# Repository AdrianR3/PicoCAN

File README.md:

# PicoCAN
PicoCAN is a custom devboard based on the RP2040 that features a built-in CAN controller and transceiver (the `MCP25625` to be exact).

## Key Features
- USB-C connection for easy programming
- RP2040 based, with the same size as the Pi Pico
- CAN BUS using MCP25625
  - Built-in 120Ω termination resistor, which can be enabled by bridging the two pins near the `CANL` pin
- Support for powering with 5V through `VSYS` pin
- 28 usable GPIO pins, including 4 ADC pins
- Two on-board LEDs (Green and Red)
  - The red LED also shares pin `24` on the board
  - The green LED is not connected to any of the PicoCAN's pins

## Using the CAN bus

To interface with the CAN bus, you can use any library that supports the MCP25625. There are a few examples that use the [MCP_CAN](https://github.com/coryjfowler/MCP_CAN_lib) library in the `./firmware_examples` folder; they are adapted from https://github.com/coryjfowler/MCP_CAN_lib.

## Building the PicoCAN
The PicoCAN can be ordered from sites like JLCPCB (and optionally assembled too). The KiCAD source files are in `./KiCAD` and the production gerber files are in `./KiCAD/prod` along with the bom.

This is what JLC PCBA gets you! These don't have the headers soldered on yet.

## Images

## Schematic

## BOM

| Name                                                                           | Purpose                                                                  | Quantity | Total Cost (USD) | Link                                                                                                                                                                                                                                                                                                                                                                                                                                                                                                                     | Distributor |
| ------------------------------------------------------------------------------ | ------------------------------------------------------------------------ | -------- | ---------------- | ------------------------------------------------------------------------------------------------------------------------------------------------------------------------------------------------------------------------------------------------------------------------------------------------------------------------------------------------------------------------------------------------------------------------------------------------------------------------------------------------------------------------ | ----------- |
| 10kΩ Resistors                                                                 | JLCPCB idle parts order to avoid ~8000 MOQ                               | 15       | 2.00             | https://jlcpcb.com/partdetail/26487-0402WGF1002TCE/C25744                                                                                                                                                                                                                                                                                                                                                                                                                                                                | JLCPCB      |
| JLCPCB PCB(A)                                                                  | PCBA for the devboard                                                    |          | 74.30            |                                                                                                                                                                                                                                                                                                                                                                                                                                                                                                                          | JLCPCB      |
| Breakaway 2.54mm Headers                                                       | Soldering to PCB for GPIO, Termination Resistor Jumper, SWD + SWCLK pins | 220      | 5.73             | https://www.amazon.com/Jabinco-Breakable-Header-Connector-Arduino/dp/B0817JG3XN/ref=sr_1_3?crid=2WKRDMD09IP3A&dib=eyJ2IjoiMSJ9.czj50ypkQJ1W7noQLo1BweZEBilxaPpO0ntqUIsbMOZ8NaUK7SirIiKj0zqjNVH7wel-Muxf7cilYZ1Gkm4LgajcBaFuuT2h6h5A3zPeYstX5vvQowuI_TuSg0Kxc1e53BEuy5Jd69yTYBwJ_uQCerRUqfk7djKjaq9QYkqNW6D93iLd-X65YBIYgty5NQg0PXmwjQjx0RvcIDNsFUhAgsMDf7z5tFzePYIG2SYMh9Q.pCbw9QGeBexphDohe_PNYFXcjPvPNsFaeCrxSnrcMaw&dib_tag=se&keywords=2.54mm+pin+header&qid=1775094589&sprefix=2.54mm+pin+header%2Caps%2C168&sr=8-3 | Amazon      |
| Socket Shorting Block Jumper Red Closed                                        | Enabling Termination Resistor built into PCB (MOQ 10)                    | 5        | 1.40             | https://www.jameco.com/webapp/wcs/stores/servlet/ProductDisplay?storeId=10001&langId=-1&catalogId=10001&pa=112432&productId=112432                                                                                                                                                                                                                                                                                                                                                                                       | Jameco      |
| Terminal Block Header 3 Position Top Screw 3.5mm Solder Straight Thru-Hole 10A | Connecting to CAN BUS (CANL, CANH, GND)                                  | 5        | 3.95             | https://www.jameco.com/webapp/wcs/stores/servlet/ProductDisplay?storeId=10001&langId=-1&catalogId=10001&pa=2094514&productId=2094514                                                                                                                                                                                                                                                                                                                                                                                     | Jameco      |

Exhaustive PCB component BOM available at `./KiCAD/prod/PicoCAN.csv`.

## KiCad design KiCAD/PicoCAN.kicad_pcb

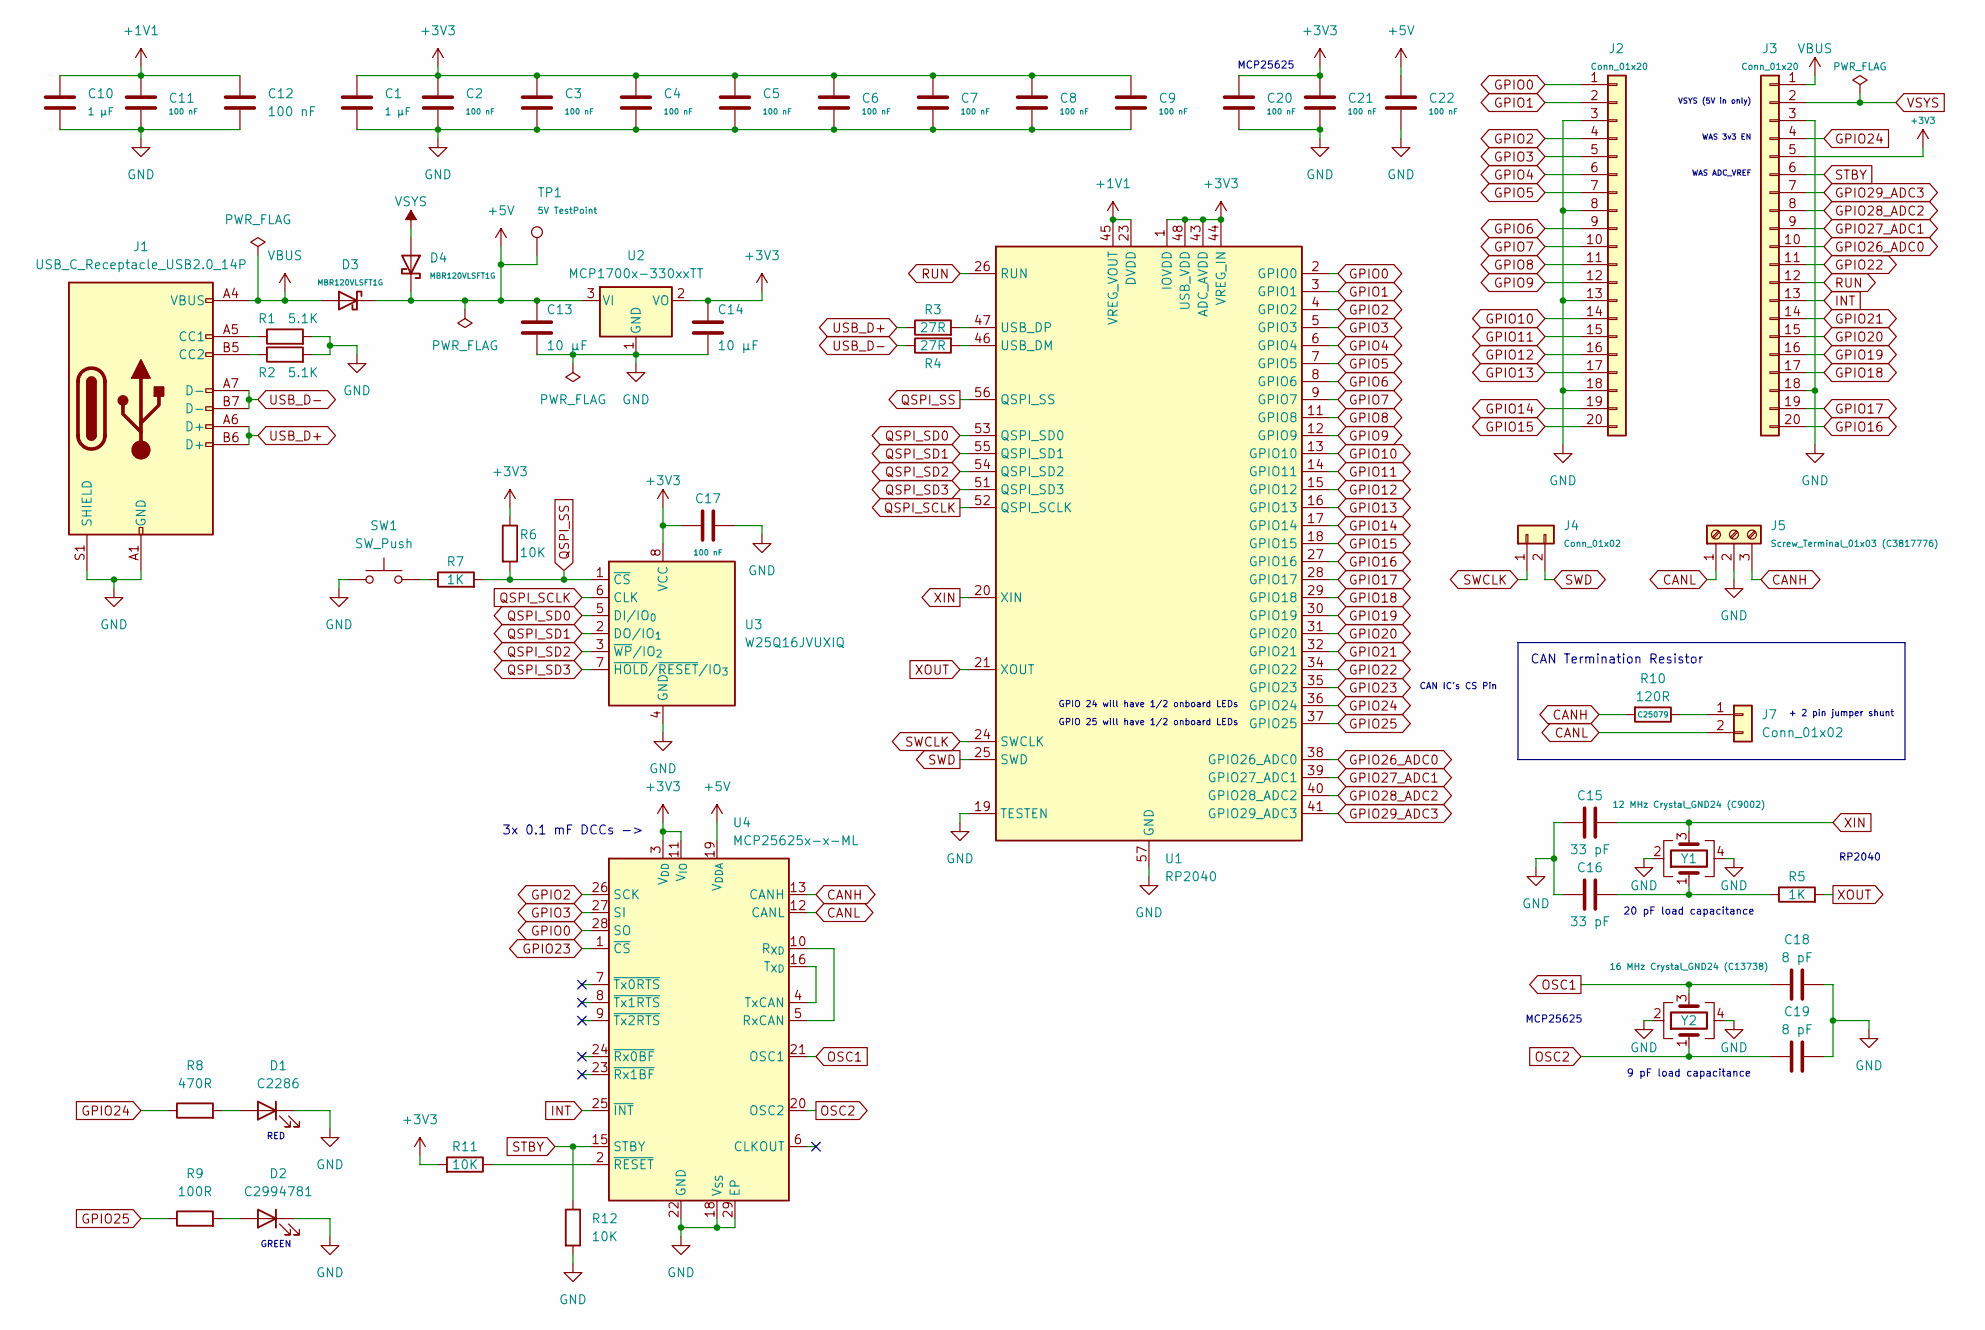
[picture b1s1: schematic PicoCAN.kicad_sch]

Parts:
C1, C10: 1 µF; C_0402_1005Metric; MPN C52923
C2, C3, C4, C5, C6, C7, C8, C9, C11, C12, C17, C20, C21, C22: 100 nF; C_0402_1005Metric; MPN C1525
C13, C14: 10 µF; C_0603_1608Metric; MPN C96446
C15, C16: 33 pF; C_0402_1005Metric; MPN C1562
C18, C19: 8 pF; C_0402_1005Metric; MPN C1578
D1: C2286; LED_0603_1608Metric_Pad1.05x0.95mm_HandSolder; MPN C2286
D2: C2994781; LED_0603_1608Metric_Pad1.05x0.95mm_HandSolder; MPN C2994781
D3, D4: MBR120VLSFT1G; D_SOD-123F; MPN C223608
J1: USB_C_Receptacle_USB2.0_14P; USB_C_Receptacle_HRO_TYPE-C-31-M-12; MPN C165948
J2, J3: Conn_01x20; PinHeader_1x20_P2.54mm_Vertical
J4, J7: Conn_01x02; PinHeader_1x02_P2.54mm_Vertical
J5: Screw_Terminal_01x03 (C3817776); CONN-TH_3P-P3.50_OSTTE030161; MPN C3817776
R1, R2: 5.1K; R_0402_1005Metric; MPN C25905
R3, R4: 27R; R_0402_1005Metric; MPN C25100
R5, R7: 1K; R_0402_1005Metric; MPN C11702
R6, R11, R12: 10K; R_0402_1005Metric; MPN C25744
R8: 470R; R_0402_1005Metric; MPN C25117
R9: 100R; R_0402_1005Metric; MPN C25076
R10: 120R; R_0402_1005Metric; MPN C25079
SW1: SW_Push; SW-SMD_L3.9-W3.0-P4.45; MPN C720477
TP1: 5V TestPoint; TestPoint_Pad_1.0x1.0mm
U1: RP2040; QFN-56-1EP_7x7mm_P0.4mm_EP3.2x3.2mm; MPN C2040
U2: MCP1700x-330xxTT; SOT-23; MPN C39051
U3: W25Q16JVUXIQ; Winbond_USON-8-1EP_3x2mm_P0.5mm_EP0.2x1.6mm; MPN C2843335
U4: MCP25625x-x-ML; QFN-28-1EP_6x6mm_P0.65mm_EP4.25x4.25mm
Y1: 12 MHz Crystal_GND24 (C9002); Crystal_SMD_3225-4Pin_3.2x2.5mm; MPN C9002
Y2: 16 MHz Crystal_GND24 (C13738); Crystal_SMD_3225-4Pin_3.2x2.5mm; MPN C13738

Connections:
+1V1: C10.1, C11.1, C12.1, U1.23 (DVDD), U1.45 (VREG_VOUT), U1.50 (DVDD)
+3V3: C1.1, C2.1, C3.1, C4.1, C5.1, C6.1, C7.1, C8.1, C9.1, C14.1, C17.2, C20.1, C21.1, J3.5, R6.1, R11.2, U1.1 (IOVDD), U1.10 (IOVDD), U1.22 (IOVDD), U1.33 (IOVDD), U1.42 (IOVDD), U1.43 (ADC_AVDD), U1.44 (VREG_IN), U1.48 (USB_VDD), U1.49 (IOVDD), U2.2 (VO), U3.8 (VCC), U4.3 (V_{DD}), U4.11 (V_{IO})
+5V: C13.1, C22.1, D3.1 (K), D4.1 (K), TP1.1 (1_1), U2.3 (VI), U4.19 (V_{DDA})
CANH: J5.3, R10.2, U4.13 (CANH)
CANL: J5.1, J7.2, U4.12 (CANL)
GND: C1.2, C2.2, C3.2, C4.2, C5.2, C6.2, C7.2, C8.2, C9.2, C10.2, C11.2, C12.2, C13.2, C14.2, C15.1, C16.1, C17.1, C18.2, C19.2, C20.2, C21.2, C22.2, D1.1 (K), D2.1 (K), J1.A1 (GND), J1.A12 (GND), J1.B1 (GND), J1.B12 (GND), J1.S1 (SHIELD), J2.3, J2.8, J2.13, J2.18, J3.3, J3.18, J5.2, R1.2, R2.2, R12.2, SW1.1, U1.19 (TESTEN), U1.57 (GND), U2.1 (GND), U3.4 (GND), U4.18 (V_{SS}), U4.22 (GND), U4.29 (EP), Y1.2, Y1.4, Y2.2, Y2.4
GPIO0: J2.1, U1.2 (GPIO0), U4.28 (SO)
GPIO1: J2.2, U1.3 (GPIO1)
GPIO2: J2.4, U1.4 (GPIO2), U4.26 (SCK)
GPIO3: J2.5, U1.5 (GPIO3), U4.27 (SI)
GPIO4: J2.6, U1.6 (GPIO4)
GPIO5: J2.7, U1.7 (GPIO5)
GPIO6: J2.9, U1.8 (GPIO6)
GPIO7: J2.10, U1.9 (GPIO7)
GPIO8: J2.11, U1.11 (GPIO8)
GPIO9: J2.12, U1.12 (GPIO9)
GPIO10: J2.14, U1.13 (GPIO10)
GPIO11: J2.15, U1.14 (GPIO11)
GPIO12: J2.16, U1.15 (GPIO12)
GPIO13: J2.17, U1.16 (GPIO13)
GPIO14: J2.19, U1.17 (GPIO14)
GPIO15: J2.20, U1.18 (GPIO15)
GPIO16: J3.20, U1.27 (GPIO16)
GPIO17: J3.19, U1.28 (GPIO17)
GPIO18: J3.17, U1.29 (GPIO18)
GPIO19: J3.16, U1.30 (GPIO19)
GPIO20: J3.15, U1.31 (GPIO20)
GPIO21: J3.14, U1.32 (GPIO21)
GPIO22: J3.11, U1.34 (GPIO22)
GPIO23: U1.35 (GPIO23), U4.1 (~CS)
GPIO24: J3.4, R8.1, U1.36 (GPIO24)
GPIO25: R9.1, U1.37 (GPIO25)
GPIO26_ADC0: J3.10, U1.38 (GPIO26_ADC0)
GPIO27_ADC1: J3.9, U1.39 (GPIO27_ADC1)
GPIO28_ADC2: J3.8, U1.40 (GPIO28_ADC2)
GPIO29_ADC3: J3.7, U1.41 (GPIO29_ADC3)
INT: J3.13, U4.25 (~INT)
unnamed: C16.2, R5.1, Y1.1
unnamed: D1.2 (A), R8.2
unnamed: D2.2 (A), R9.2
unnamed: J1.A5 (CC1), R1.1
unnamed: J1.B5 (CC2), R2.1
unnamed: J7.1, R10.1
unnamed: R7.1, SW1.2
unnamed: R4.2, U1.46 (USB_DM)
unnamed: R3.2, U1.47 (USB_DP)
unnamed: U4.5 (RxCAN), U4.10 (R_{XD})
unnamed: U4.4 (TxCAN), U4.16 (T_{XD})
unnamed: R11.1, U4.2 (~RESET)
OSC1: C18.1, U4.21 (OSC1), Y2.3
OSC2: C19.1, U4.20 (OSC2), Y2.1
QSPI_SCLK: U1.52 (QSPI_SCLK), U3.6 (CLK)
QSPI_SD0: U1.53 (QSPI_SD0), U3.5 (DI/IO_{0})
QSPI_SD1: U1.55 (QSPI_SD1), U3.2 (DO/IO_{1})
QSPI_SD2: U1.54 (QSPI_SD2), U3.3 (~WP/IO_{2})
QSPI_SD3: U1.51 (QSPI_SD3), U3.7 (~HOLD/~RESET/IO_{3})
QSPI_SS: R6.2, R7.2, U1.56 (QSPI_SS), U3.1 (~CS)
RUN: J3.12, U1.26 (RUN)
STBY: J3.6, R12.1, U4.15 (STBY)
SWCLK: J4.1, U1.24 (SWCLK)
SWD: J4.2, U1.25 (SWD)
USB_D+: J1.A6 (D+), J1.B6 (D+), R3.1
USB_D-: J1.A7 (D-), J1.B7 (D-), R4.1
VBUS: D3.2 (A), J1.A4 (VBUS), J1.A9 (VBUS), J1.B4 (VBUS), J1.B9 (VBUS), J3.1
VSYS: D4.2 (A), J3.2
XIN: C15.2, U1.20 (XIN), Y1.3
XOUT: R5.2, U1.21 (XOUT)

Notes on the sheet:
WAS 3v3 EN
CAN IC's CS Pin
GPIO 24 will have 1/2 onboard LEDs
3x 0.1 mF DCCs ->
CAN Termination Resistor
9 pF load capacitance
VSYS (5V in only)
GREEN
+ 2 pin jumper shunt
MCP25625
20 pF load capacitance
GPIO 25 will have 1/2 onboard LEDs
RED
WAS ADC_VREF
RP2040

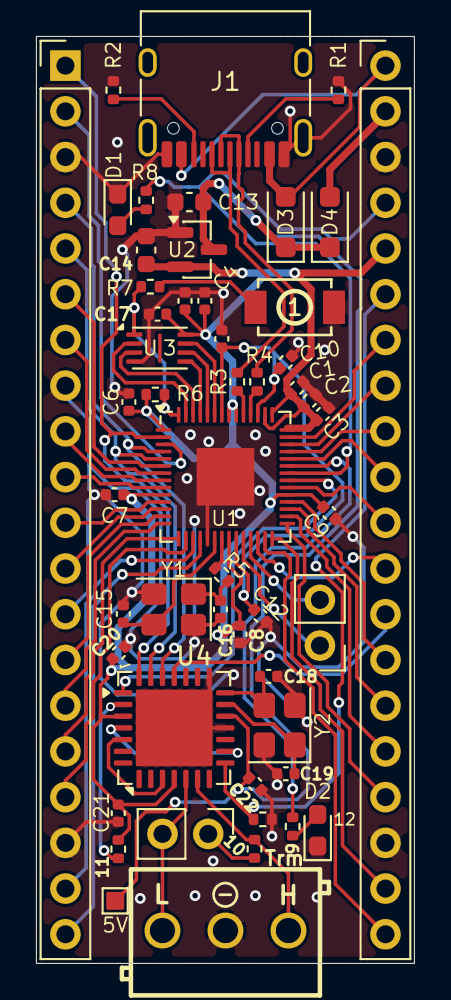
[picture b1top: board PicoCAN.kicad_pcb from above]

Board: 2 copper layers, 21.0 x 51.5 mm, 52 parts (0 on the bottom side), 67 nets.

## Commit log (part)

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2026-03-17 Add gitignore
2026-03-17 Initial schematic
    Everything before breaking out the GPIO pins
2026-03-19 Add MCP25625 and more progress
2026-03-29 Finished MCP25625
2026-03-30 Footprints and schematic (w/load caps) finished
2026-03-30 PCB Layout
2026-03-31 Finished Traces
2026-04-01 Finished PCB
2026-04-02 Add basic readme
2026-04-02 Add firmware examples
2026-04-02 Add images
2026-04-02 Add kicad-render.png
2026-04-02 Scale down images
2026-04-02 Finished PCB from earlier
2026-04-02 Add PROD files
2026-04-02 Add cover image
2026-04-03 Enhance BOM
2026-04-03 Upload schematic image to assets
2026-04-03 Add schematic image
